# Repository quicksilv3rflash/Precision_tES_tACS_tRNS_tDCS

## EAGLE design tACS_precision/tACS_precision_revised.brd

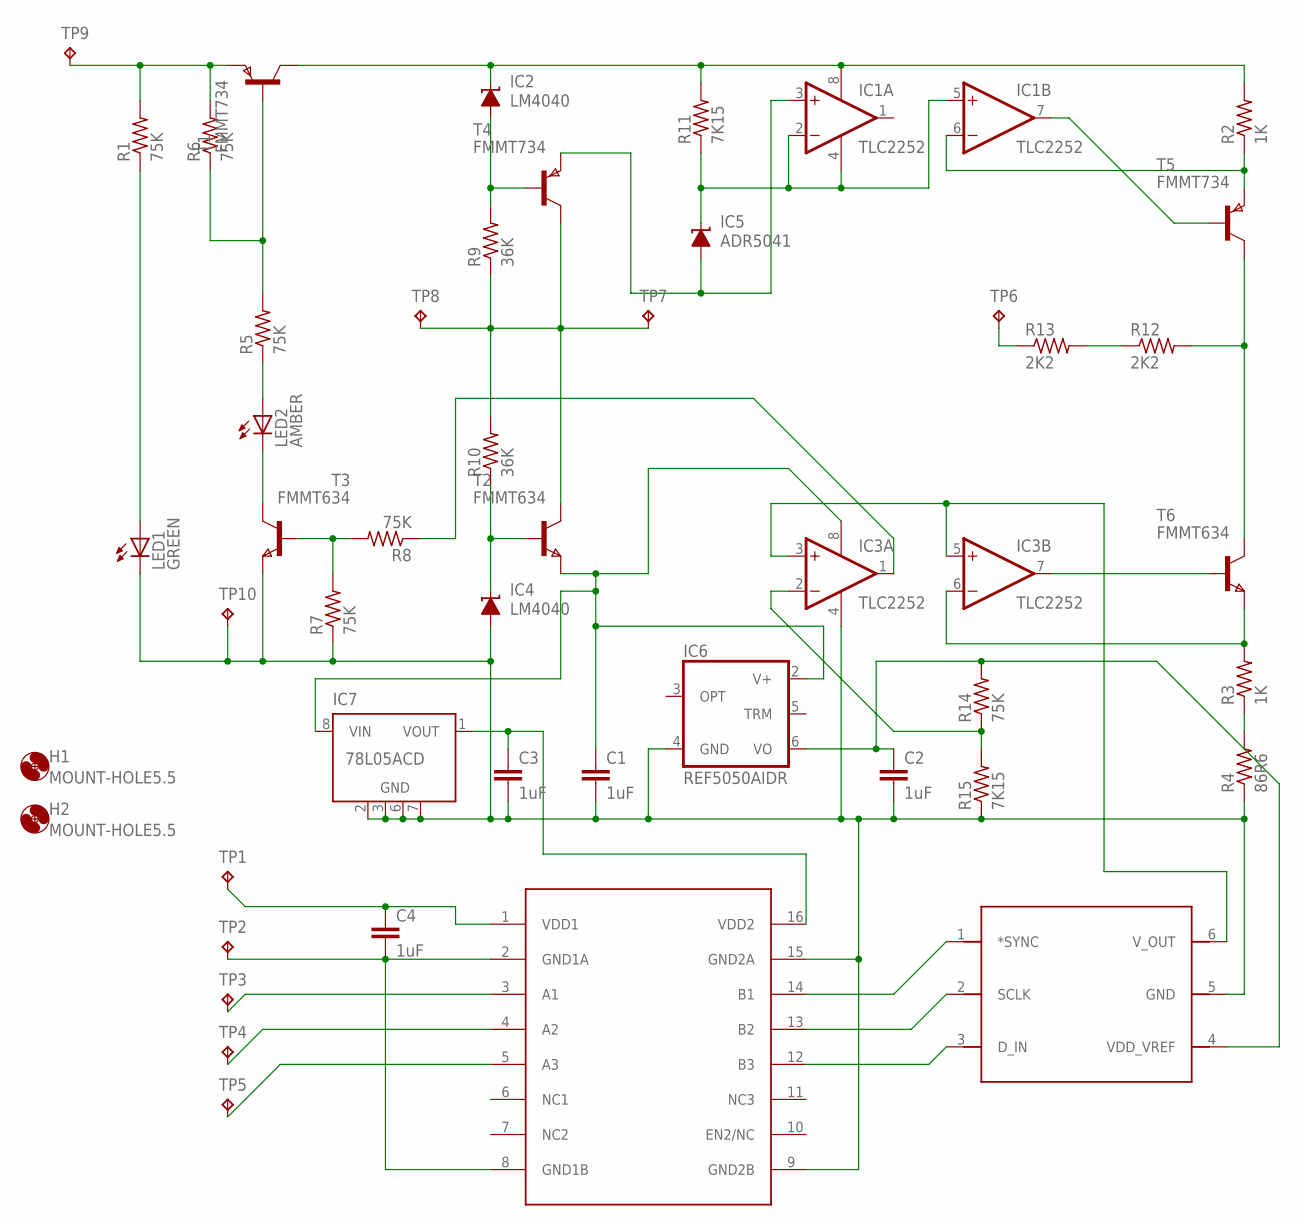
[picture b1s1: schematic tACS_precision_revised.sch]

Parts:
C1, C2, C3, C4: 1uF; C1608
H1, H2: MOUNT-HOLE5.5; 5,5
IC1, IC3: TLC2252; SO08
IC2, IC4: LM4040; DBZ_R-PDSO-G3
IC5: ADR5041; DBZ_R-PDSO-G3
IC6: REF5050AIDR; SO08
IC7: 78L05ACD; SO08
LED1: GREEN; SML0603
LED2: AMBER; SML1206
R1, R5, R6, R7, R8, R14: 75K; R0603
R2, R3: 1K; R0603
R4: 86R6; R0603
R9, R10: 36K; R0603
R11, R15: 7K15; R0603
R12, R13: 2K2; R2512
T1, T4, T5: FMMT734; SOT-23
T2, T3, T6: FMMT634; SOT-23
TP1, TP2, TP3, TP4, TP5, TP6, TP7, TP8, TP9, TP10: TPPAD1-13Y; P1-13Y
U$1: DAC7311; SC70-6
U$2: SI8630BD; SOIC16R

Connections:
unnamed: LED1.A, R1.1
unnamed: LED2.C, T3.1 (C)
unnamed: C1.2, C2.2, C3.2, IC3.4 (V-), IC4.2 (A), IC6.4 (GND), IC7.2 (GND), IC7.3 (GND), IC7.6 (GND), IC7.7 (GND), LED1.C, R4.1, R7.1, R15.1, T3.2 (E), TP10.TP, U$1.5 (GND), U$2.9 (GND2B), U$2.15 (GND2A)
unnamed: R1.2, R6.2, T1.2 (E), TP9.TP
unnamed: R5.2, R6.1, T1.3 (B)
unnamed: LED2.A, R5.1
unnamed: R7.2, R8.2, T3.3 (B)
unnamed: IC1.8 (V+), IC2.1 (C), R2.2, R11.2, T1.1 (C)
unnamed: IC4.1 (C), R10.1, T2.3 (B)
unnamed: IC2.2 (A), R9.2, T4.3 (B)
unnamed: R9.1, R10.2, T2.1 (C), T4.1 (C), TP7.TP, TP8.TP
unnamed: IC3.1 (OUT), R8.1
unnamed: IC1.6 (-IN), R2.1, T5.2 (E)
unnamed: IC1.7 (OUT), T5.3 (B)
unnamed 14: IC1.3 (+IN), IC5.2 (A), T4.2 (E); also elsewhere on the board
unnamed 15: IC1.2 (-IN), IC1.4 (V-), IC1.5 (+IN), IC5.1 (C), R11.1; also elsewhere on the board
unnamed: C1.1, IC3.8 (V+), IC6.2 (V+), IC7.8 (VIN), T2.2 (E)
unnamed: IC3.6 (-IN), R3.2, T6.2 (E)
unnamed: R3.1, R4.2
unnamed: IC3.7 (OUT), T6.3 (B)
unnamed: IC3.3 (+IN), IC3.5 (+IN), U$1.6 (V_OUT)
unnamed: R12.1, R13.2
unnamed: R12.2, T5.1 (C), T6.1 (C)
unnamed: R13.1, TP6.TP
unnamed: IC3.2 (-IN), R14.1, R15.2
unnamed: C2.1, IC6.6 (VO), R14.2, U$1.4 (VDD_VREF)
unnamed: C4.1, TP1.TP, U$2.1 (VDD1)
unnamed: C4.2, TP2.TP, U$2.2 (GND1A), U$2.8 (GND1B)
unnamed: TP3.TP, U$2.3 (A1)
unnamed: TP4.TP, U$2.4 (A2)
unnamed: U$1.1 (*SYNC), U$2.14 (B1)
unnamed: U$1.2 (SCLK), U$2.13 (B2)
unnamed: U$1.3 (D_IN), U$2.12 (B3)
unnamed: C3.1, IC7.1 (VOUT), U$2.16 (VDD2)
unnamed: TP5.TP, U$2.5 (A3)

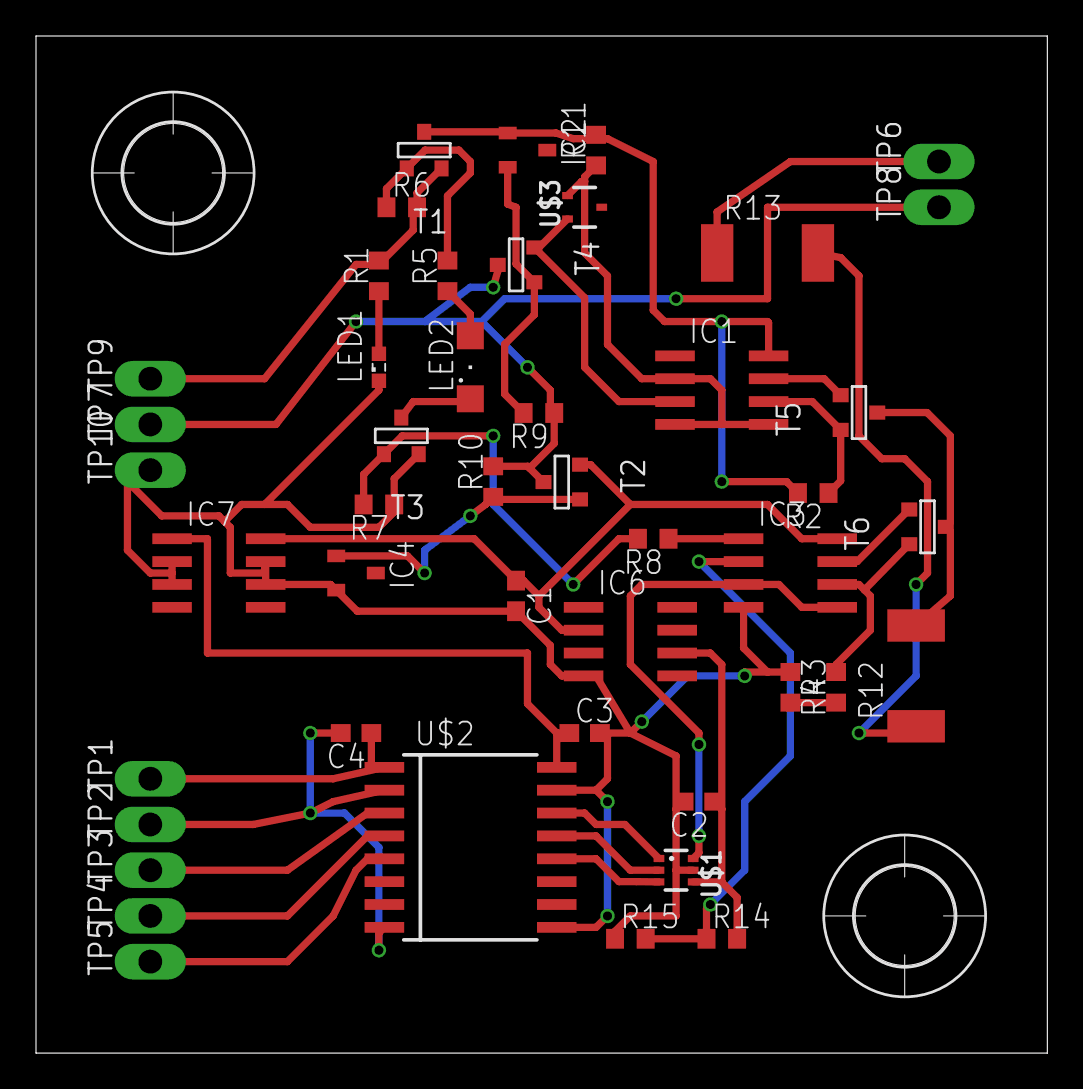
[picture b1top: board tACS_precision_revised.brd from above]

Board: 2 copper layers, 56.2 x 56.5 mm, 48 parts (0 on the bottom side), 35 nets.

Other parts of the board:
U$3: ADR5041; SC70-3

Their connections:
unnamed 14: U$3.ANODE; also elsewhere on the board
unnamed 15: U$3.CATHODE; also elsewhere on the board

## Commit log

2017-01-19 :confetti_ball: Added .gitattributes & .gitignore files
2017-01-19 added files
2017-01-20 fixed board silkscreens
2017-01-20 including revised board files
2017-01-30 patched board layout
2017-01-31 test firmware generates sawtooth wave
2017-02-08 Board fixed, firmware written, all tested
2017-02-09 proofread firmware code comments
2017-02-14 not yet working.
2017-02-14 outputs sine wave, tested, works
2017-02-14 tweaked to see if decreasing TCCR2B interrupt rate improved stability. it didn't.
2017-02-14 squarewave testing
2017-02-14 pretty pretty sine waves
2017-02-17 condensed transmit functions
2017-02-27 Now a working GUI and drivers
2017-02-27 separated deprecated file versions
2017-03-13 push commits before final testing
2017-03-22 "detail oriented"
2017-03-23 acceptable
2017-03-23 The core DAC format function!
2017-03-23 complete.
2017-03-25 ".py"
2018-08-16 Add files via upload
    Driver firmware and schematics to produce a two-channel tACS device
2026-06-09 Create LICENSE.md
    Creative Commons Zero v1.0 Universal
